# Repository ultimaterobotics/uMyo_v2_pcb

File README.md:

# PCB for uMyo (v2)

This is a KiCAD 6 project for the first produced batch of uMyo devices. There are some things worth improving, but overall it works as intended.

PCB is licensed under CERN-OHL-P-2.0 - we use MIT license for our software/firmware projects, but it seems that for hardware it doesn't work well, so we applied this option. In our understanding, it should permit anyone to use this design as a whole or incorporate its parts into other projects with no restrictions (including commercial use), except for claiming that it was not derived from our project. If you want to use it but something in this license prevents you from doing that - please contact us, we'll see what can be done about it.

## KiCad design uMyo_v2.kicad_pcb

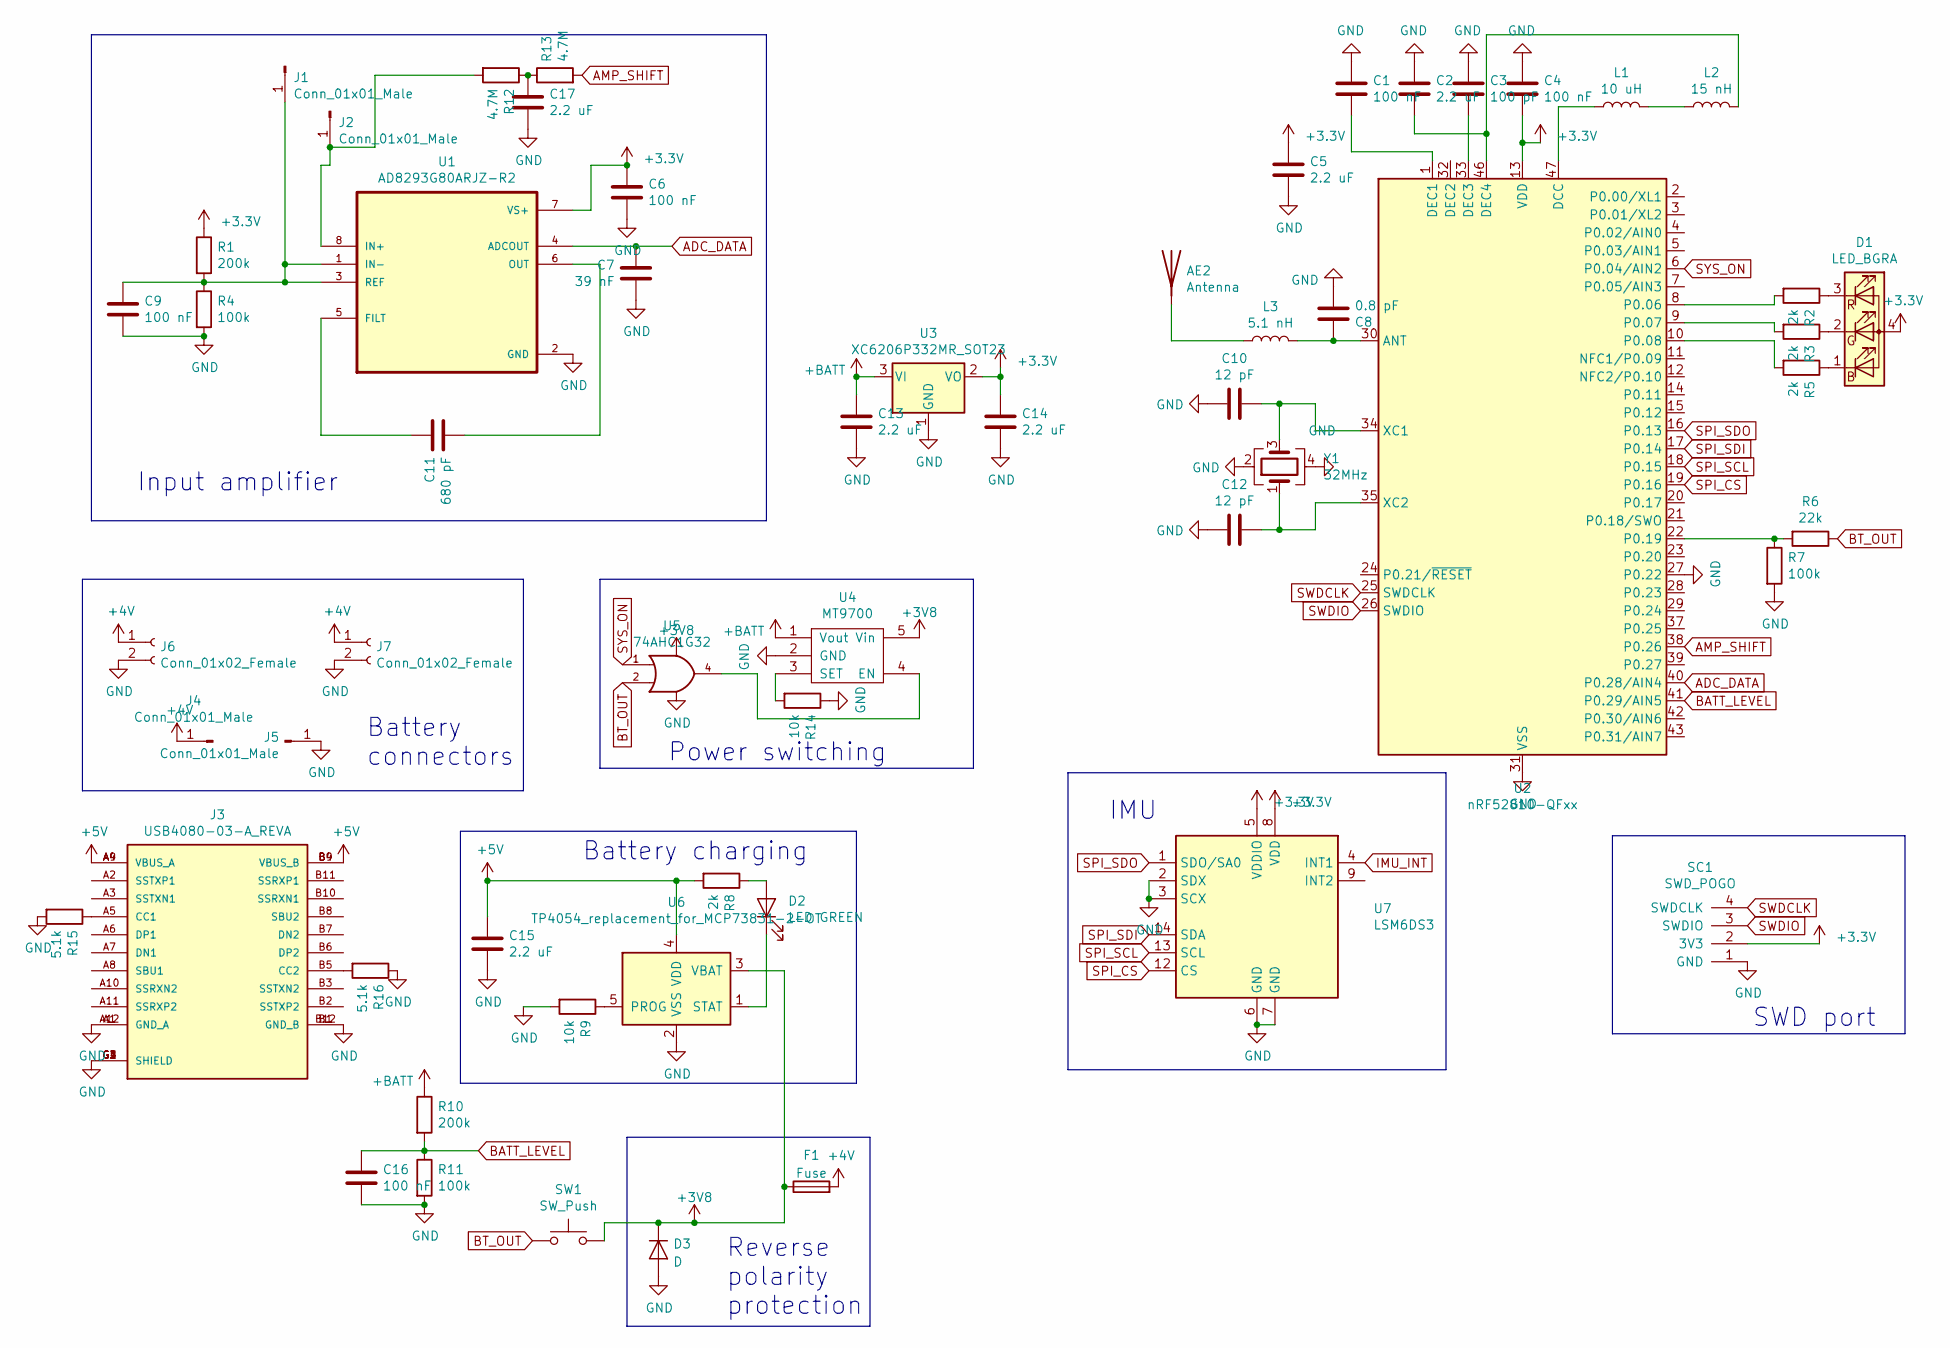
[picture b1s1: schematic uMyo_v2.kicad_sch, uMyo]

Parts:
AE2: Antenna; XCVR_YC0010AA; JLCPN C504003
C1, C4, C6, C9, C16: 100 nF; C_0402_1005Metric; JLCPN C1525
C2, C5, C13, C14, C15, C17: 2.2 uF; C_0402_1005Metric; JLCPN C12530
C3: 100 pF; C_0402_1005Metric; JLCPN C1546
C7: 39 nF; C_0402_1005Metric; JLCPN C117753
C8: 0.8 pF; C_0402_1005Metric; JLCPN C88902
C10, C12: 12 pF; C_0402_1005Metric; JLCPN C1547
C11: 680 pF; C_0402_1005Metric; JLCPN C113781
D1: LED_BGRA; LED_RGB_0603_a4; JLCPN C282128
D2: LED GREEN; LED_0603_1608Metric; JLCPN C72043
D3: D; D_SOD-323; JLCPN C191023
F1: Fuse; Fuse_0603_1608Metric; JLCPN C207011
J1, J2: Conn_01x01_Male; textile_button_6mm
J3: USB4080-03-A_REVA; PARTREV A; JLCPN C183607
J4, J5: Conn_01x01_Male; conn_06_20
J6, J7: Conn_01x02_Female; JST_PH_S2B-PH-K_1x02_P2.00mm_Horizontal; JLCPN C173752
L1: 10 uH; L_0603_1608Metric; JLCPN C1035
L2: 15 nH; L_0402_1005Metric; JLCPN C27143
L3: 5.1 nH; L_0402_1005Metric; JLCPN C86066
R1, R10: 200k; R_0402_1005Metric; JLCPN C25764
R2, R3, R5, R8: 2k; R_0402_1005Metric; JLCPN C4109
R4, R7, R11: 100k; R_0402_1005Metric; JLCPN C25741
R6: 22k; R_0402_1005Metric; JLCPN C25768
R9, R14: 10k; R_0402_1005Metric; JLCPN C25744
R12, R13: 4.7M; R_0402_1005Metric; JLCPN C227116
R15, R16: 5.1k; R_0402_1005Metric; JLCPN C25905
SC1: SWD_POGO
SW1: SW_Push; SW_SPST_CK_RS282G05A3; JLCPN C2845294
U1: AD8293G80ARJZ-R2; SOT-23-8; JLCPN C141950
U2: nRF52810-QFxx; QFN-48-1EP_6x6mm_Pitch0.4mm; JLCPN C141828
U3: XC6206P332MR_SOT23; SOT-23; JLCPN C5446
U4: MT9700; SOT-23-5; JLCPN C89855
U5: 74AHC1G32; SOT-23-5; JLCPN C507209
U6: TP4054_replacement_for_MCP73831-2-OT; SOT-23-5; JLCPN C668215
U7: LSM6DS3; LGA-14_3x2.5mm_P0.5mm_LayoutBorder3x4y; JLCPN C967633
Y1: 32MHz; Crystal_SMD_2016-4Pin_2.0x1.6mm; JLCPN C843260

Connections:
+3V3: C4.1, C5.2, C6.2, C14.2, D1.4 (A), R1.1, SC1.2 (3V3), U1.7 (VS+), U2.13 (VDD), U2.36 (VDD), U2.48 (VDD), U3.2 (VO), U7.5 (VDDIO), U7.8 (VDD)
+3V8: D3.1 (K), F1.1, SW1.2, U4.5 (Vin), U5.5 (VCC), U6.3 (VBAT)
+4V: F1.2, J4.1, J6.1, J7.1
+5V: C15.2, J3.A4 (VBUS_A), J3.A9 (VBUS_A), J3.B4 (VBUS_B), J3.B9 (VBUS_B), R8.2, U6.4 (VDD)
+BATT: C13.2, R10.1, U3.3 (VI), U4.1 (Vout)
ADC_DATA: C7.1, U1.4 (ADCOUT), U2.40 (P0.28/AIN4)
AMP_SHIFT: R13.2, U2.38 (P0.26)
BATT_LEVEL: C16.2, R10.2, R11.1, U2.41 (P0.29/AIN5)
BT_OUT: R6.1, SW1.1, U5.2
GND: C1.2, C2.2, C3.2, C4.2, C5.1, C6.1, C7.2, C8.2, C9.1, C10.1, C12.1, C13.1, C14.1, C15.1, C16.1, C17.1, D3.2 (A), J3.A1 (GND_A), J3.A12 (GND_A), J3.B1 (GND_B), J3.B12 (GND_B), J3.G1 (SHIELD), J3.G2 (SHIELD), J3.G3 (SHIELD), J3.G4 (SHIELD), J5.1, J6.2, J7.2, R4.2, R7.2, R9.2, R11.2, R14.1, R15.2, R16.1, SC1.1 (GND), U1.2 (GND), U2.27 (P0.22), U2.31 (VSS), U2.45 (VSS), U2.49 (VSS), U3.1 (GND), U4.2 (GND), U5.3 (GND), U6.2 (VSS), U7.2 (SDX), U7.3 (SCX), U7.6 (GND), U7.7 (GND), Y1.2, Y1.4
IMU_INT: U7.4 (INT1)
unnamed: AE2.1 (A), L3.1
unnamed: C1.1, U2.1 (DEC1)
unnamed: C2.1, L2.2, U2.46 (DEC4)
unnamed: C3.1, U2.33 (DEC3)
unnamed: C8.1, L3.2, U2.30 (ANT)
unnamed: C9.2, J1.1, R1.2, R4.1, U1.1 (IN-), U1.3 (REF)
unnamed: C10.2, U2.34 (XC1), Y1.3
unnamed: C11.1, U1.5 (FILT)
unnamed: C11.2, U1.6 (OUT)
unnamed: C12.2, U2.35 (XC2), Y1.1
unnamed: C17.2, R12.1, R13.1
unnamed: D1.1 (BK), R5.1
unnamed: D1.2 (GK), R3.1
unnamed: D1.3 (RK), R2.1
unnamed: D2.1 (K), U6.1 (STAT)
unnamed: D2.2 (A), R8.1
unnamed: J2.1, R12.2, U1.8 (IN+)
unnamed: J3.A5 (CC1), R15.1
unnamed: J3.B5 (CC2), R16.2
unnamed: L1.1, U2.47 (DCC)
unnamed: L1.2, L2.1
unnamed: R2.2, U2.8 (P0.06)
unnamed: R3.2, U2.9 (P0.07)
unnamed: R5.2, U2.10 (P0.08)
unnamed: R6.2, R7.1, U2.22 (P0.19)
unnamed: R9.1, U6.5 (PROG)
unnamed: R14.2, U4.3 (SET)
unnamed: U4.4 (EN), U5.4
SPI_CS: U2.19 (P0.16), U7.12 (CS)
SPI_SCL: U2.18 (P0.15), U7.13 (SCL)
SPI_SDI: U2.17 (P0.14), U7.14 (SDA)
SPI_SDO: U2.16 (P0.13), U7.1 (SDO/SA0)
SWDCLK: SC1.4 (SWDCLK), U2.25 (SWDCLK)
SWDIO: SC1.3 (SWDIO), U2.26 (SWDIO)
SYS_ON: U2.6 (P0.04/AIN2), U5.1

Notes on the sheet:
SWD port
Power switching
Battery connectors
Battery charging
IMU
Reverse polarity protection
Input amplifier

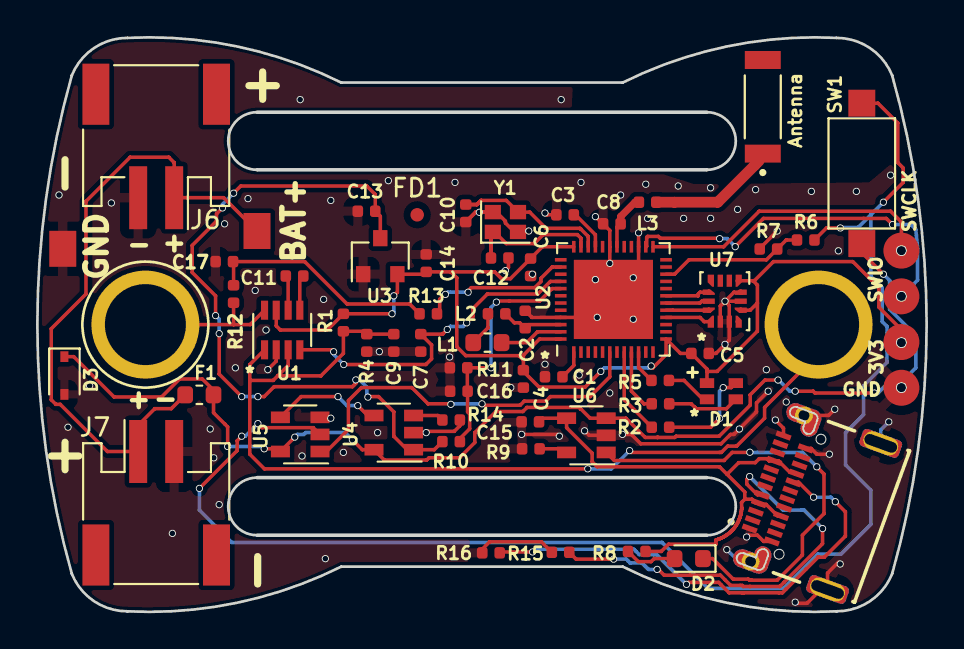
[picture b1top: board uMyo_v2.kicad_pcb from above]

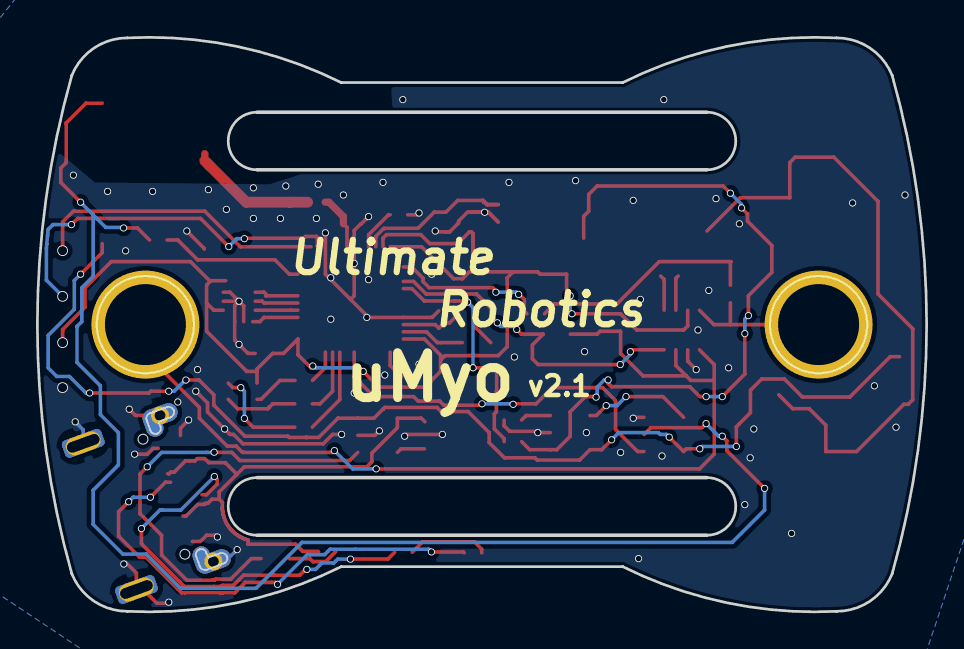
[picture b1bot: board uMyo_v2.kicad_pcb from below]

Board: 2 copper layers, 49.4 x 31.9 mm, 59 parts (2 on the bottom side), 45 nets.

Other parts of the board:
FD1: Fiducial_0.75mm_Dia_1.5mm_Outer

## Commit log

2022-11-23 produced PCB version
2023-02-15 no actual changes, for github to pickup type
